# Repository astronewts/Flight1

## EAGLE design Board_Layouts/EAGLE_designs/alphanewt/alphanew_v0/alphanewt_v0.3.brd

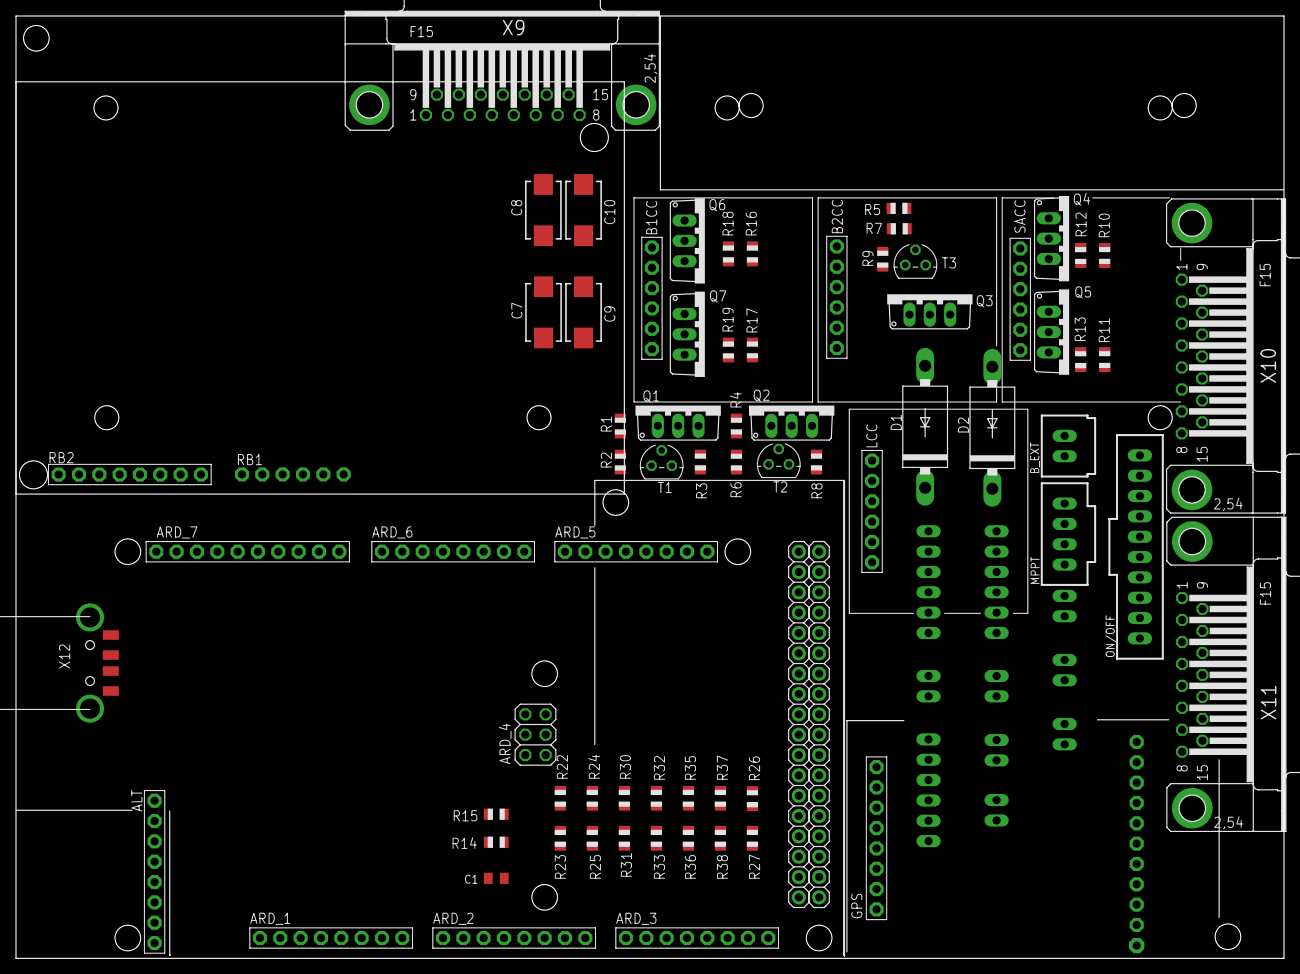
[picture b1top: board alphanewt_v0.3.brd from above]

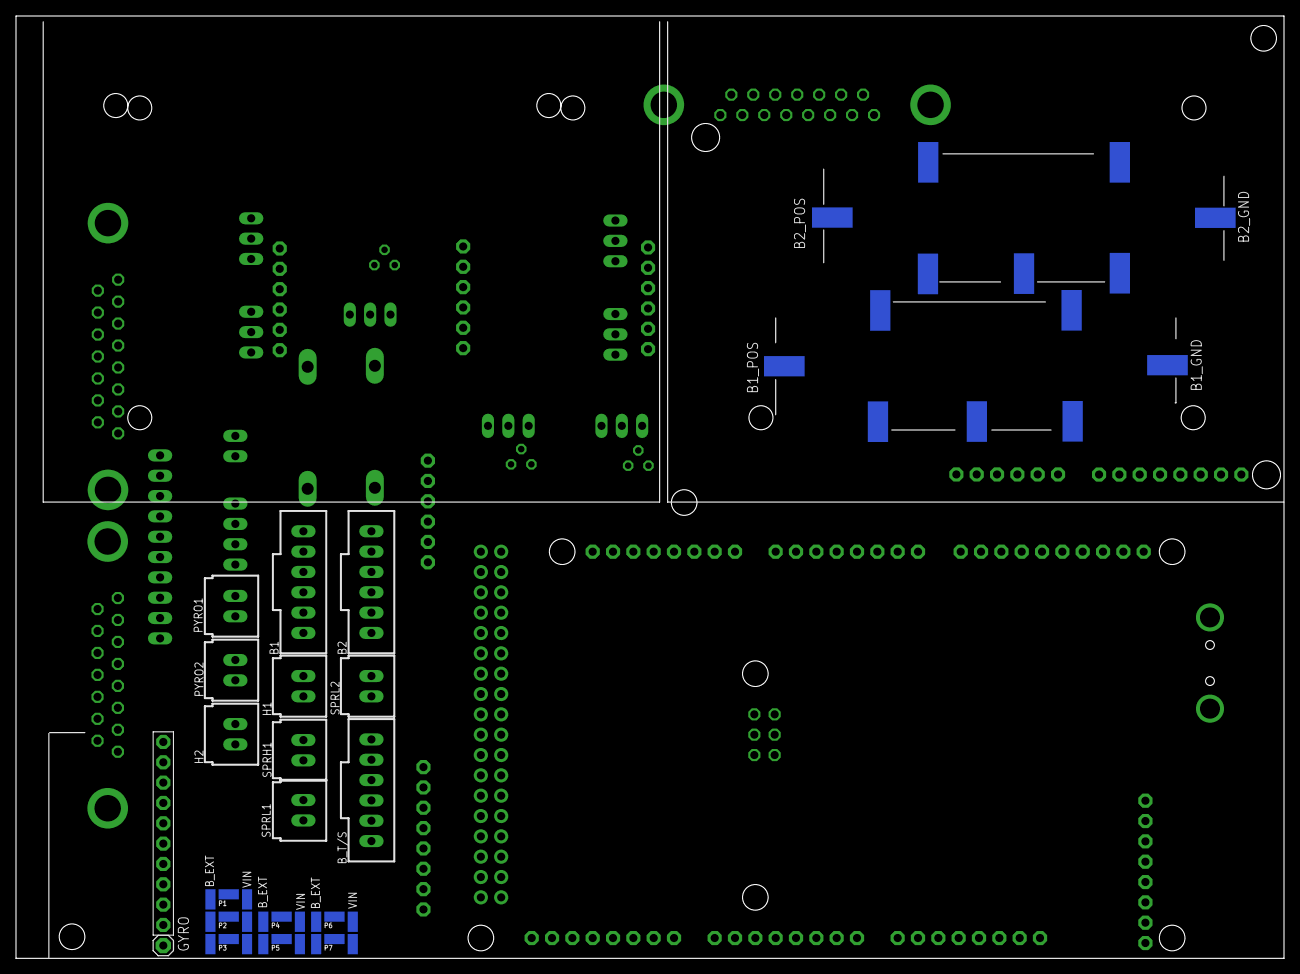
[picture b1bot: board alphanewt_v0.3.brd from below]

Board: 2 copper layers, 158.4 x 117.7 mm, 121 parts (47 on the bottom side), 80 nets, no tracks yet.

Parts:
ALT: 1X08-BIG
ARD_1, ARD_2, ARD_3, ARD_5, ARD_6: 1X08-BIG
ARD_4: 2X03
ARD_7: PINHD-1X10; 1X10-BIG
ARD_8, ARD_9: 1X18-BIG
B1, B2: C-GRID-06-70543; 70543-06
B1CC, B2CC: 1X06-BIG
B1_CELL_1, B1_CELL_2, B1_CELL_3, B1_GND, B1_IN_NEG, B1_IN_POS, B1_POS, B2_CELL_1, B2_CELL_2, B2_GND, B2_IN_NEG, B2_IN_POS, B2_POS, B3_CELL_3: SMD2,54-5,08
B_EXT: C-GRID-02-70543; 70543-02
B_T/S: C-GRID-06-70543; 70543-06
C1: 4.7uF; C0805K
C7, C8, C9, C10: CT7343
D1, D2: 1N5400; DO201-15
GPS: 1X08-BIG
GYRO: PINHD-1X10; 1X10-BIG
GYRO_2: 1X01
H1, H2: C-GRID-02-70543; 70543-02
LCC: 1X06-BIG
MPPT: C-GRID-04-70543; 70543-04
ON/OFF: C-GRID-10-70543; 70543-10
PEXT1, PEXT2, PEXT3, PEXT4, PEXT5, PEXT6, PEXT7: SMD1,27-2,54
PO1, PO2, PO3, PO4, PO5, PO6, PO7: SMD1,27-2,54
PVIN1, PVIN2, PVIN3, PVIN4, PVIN5, PVIN6, PVIN7: SMD1,27-2,54
PYRO1, PYRO2: C-GRID-02-70543; 70543-02
Q1, Q2, Q3, Q4, Q5, Q6, Q7: TIP41C; TO220AV
R1, R2, R3, R4, R5, R6, R7, R8, R9: 150; R0805
R10, R11, R16, R17: 120; R0805
R12, R13, R18, R19: 10k; R0805
R14: 1.7M; R0805
R15: 470k; R0805
R22, R24, R26, R30, R32, R35, R37: 6800; R0805
R23, R25, R27, R31, R33, R36, R38: 120000; R0805
RB1: 1X06-CLEANBIG
RB2: 1X08-BIG
SACC: 1X06-BIG
SPRH1: C-GRID-02-70543; 70543-02
SPRL1, SPRL2: C-GRID-02-70543; 70543-02
T1, T2, T3: 2N3904; TO92
X9, X10, X11: F15HP
X12: USB-A; MOLEX_480371000

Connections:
+3.3V: ALT.2, ARD_1.4, B1CC.1, B2CC.1, GPS.1, LCC.1, SACC.1
+5V: ARD_1.5, ARD_8.1, ARD_9.1, R22.2, R24.2, R26.2, R30.2, R32.2, R35.2, R37.2, RB2.2
ALT_CS: ALT.7, ARD_8.7
ALT_MISO: ALT.5, ARD_8.9
ALT_MOSI: ALT.6, ARD_8.8
ALT_SCK: ALT.4, ARD_8.10
B1_CHRG_IN: B1.1, B1CC.6, B1_POS.1, C7.+, C9.+
B1_CHRG_OUT: B1CC.5, B2CC.5, ON/OFF.1
B1_GND: B1.6, B1_GND.1, C7.-, C9.-, ON/OFF.2
B1_TO_LOAD: D1.A, ON/OFF.5
B2_CHRG_IN: B2.1, B2CC.6, B2_POS.1, C8.+, C10.+
B2_GND: B2.6, B2_GND.1, C8.-, C10.-, ON/OFF.4
B2_TO_LOAD: D2.A, ON/OFF.7
BATT_1_TS1: ARD_3.1, B_T/S.1, R30.1, R31.2
BATT_1_TS2: ARD_3.2, B_T/S.3, R32.1, R33.2
BATT_2_TS1: ARD_3.3, B_T/S.4, R35.1, R36.2
BATT_2_TS2: ARD_3.4, B_T/S.6, R37.1, R38.2
BATT_CHRG_PWR: B1_IN_POS.1, B2_IN_POS.1, MPPT.1
BATT_CHRG_PWR_RTN: B1_IN_NEG.1, B2_IN_NEG.1, MPPT.2
BATT_EXT_PWR: B_EXT.1, PEXT1.1, PEXT2.1, PEXT3.1, PEXT4.1, PEXT5.1, PEXT6.1, PEXT7.1, X10.1, X10.3
CUTDOWN_1_FIRE: ARD_6.5, R1.2
CUTDOWN_2_FIRE: ARD_6.4, R4.2
FLT_CMP_TEMP: ARD_2.7, R26.1, R27.2
GND: ALT.3, ARD_1.6, ARD_1.7, ARD_7.4, ARD_8.18, ARD_9.18, B1CC.2, B2CC.2, B_EXT.2, B_T/S.2, B_T/S.5, C1.2, GPS.8, GYRO.1, LCC.2, ON/OFF.6, ON/OFF.8, ON/OFF.10, Q1.E, Q2.E, Q3.E, Q4.E, Q5.E, Q6.E, Q7.E, R3.1, R8.1, R9.1, R12.1, R13.1, R15.1, R18.1, R19.1, R23.1, R25.1, R27.1, R31.1, R33.1, R36.1, R38.1, RB1.6, RB2.1, RB2.8, SACC.2, X9.2, X9.4, X10.2, X10.4, X12.4
GYRO_PWR: ARD_8.5, GYRO.2
HEATER_1_PWR: H1.1, PO4.1, X11.8
HEATER_1_PWR_RTN: H1.2, Q4.C, X11.9
HEATER_2_PWR: H2.1, PO5.1, X11.10
HEATER_2_PWR_RTN: H2.2, Q5.C, X11.11
HEATER_CONTROL_1: ARD_7.10, R10.2
HEATER_CONTROL_2: ARD_6.3, R11.2
LOAD_IN: D1.C, D2.C, LCC.6
MISO: ARD_4.1, ARD_7.6
MOSI: ARD_4.4, ARD_7.7
unnamed: R4.1, R6.2, T2.2
unnamed: R1.1, R2.2, T1.2
unnamed: Q4.B, R10.1, R12.2
unnamed: Q2.B, R6.1, R8.2, T2.3
unnamed: Q5.B, R11.1, R13.2
unnamed: Q1.B, R2.1, R3.2, T1.3
unnamed: Q6.B, R16.1, R18.2
unnamed: R5.1, R7.2, T3.2
unnamed: Q3.B, R7.1, R9.2, T3.3
unnamed: B1.5, B1_CELL_1.1
unnamed: Q7.B, R17.1, R19.2
unnamed: B1.4, B1_CELL_2.1
unnamed: B2.3, B3_CELL_3.1
unnamed: B2.4, B2_CELL_2.1
unnamed: B2.5, B2_CELL_1.1
unnamed: B1.3, B1_CELL_3.1
PYRO_1_PWR: PO1.1, PYRO1.1, X11.1
PYRO_1_PWR_RTN: PYRO1.2, Q1.C, T1.1, X11.2
PYRO_2_PWR: PO2.1, PYRO2.1, X11.3
PYRO_2_PWR_RTN: PYRO2.2, Q2.C, T2.1, X11.4
RESET: ARD_1.3, ON/OFF.9
RX0: ARD_6.8, X12.2
RX1: ARD_5.6, GPS.5
RX3: ARD_5.2, RB1.2
S/A_PWR_IN: SACC.6, X10.6, X10.8, X10.10
S/A_PWR_OUT: MPPT.3, SACC.5
S/A_PWR_RTN: MPPT.4, X10.7, X10.9, X10.11
SCK: ARD_4.3, ARD_7.5
SCL: ARD_5.8, B1CC.3, B2CC.3, GYRO.4, LCC.3, SACC.3
SDA: ARD_5.7, B1CC.4, B2CC.4, GYRO.3, LCC.4, SACC.4
SPARE_1_PWR: PO6.1, SPRL1.1, X11.12
SPARE_1_PWR_RTN: Q6.C, SPRL1.2, X11.13
SPARE_2_PWR: PO7.1, SPRL2.1, X11.14
SPARE_2_PWR_RTN: Q7.C, SPRL2.2, X11.15
SPARE_HIGH_1_CONTROL: ARD_9.2, R5.2
SPARE_HIGH_1_PWR: PO3.1, SPRH1.1, X11.5
SPARE_HIGH_1_PWR_RTN: Q3.C, SPRH1.2, T3.1, X11.6
SPARE_LOW_1_CONTROL: ARD_9.3, R16.2
SPARE_LOW_2_CONTROL: ARD_9.4, R17.2
TEMP_EXT_1: ARD_2.8, R22.1, R23.2, X9.1
TEMP_EXT_2: ARD_2.6, R24.1, R25.2, X9.3
TX0: ARD_6.7, X12.3
TX1: ARD_5.5, GPS.4
TX3: ARD_5.1, RB1.3
VIN: ARD_1.8, LCC.5, PVIN1.1, PVIN2.1, PVIN3.1, PVIN4.1, PVIN5.1, PVIN6.1, PVIN7.1, R14.2
VIN_VOLTAGE_TLM: ARD_2.4, C1.1, R14.1, R15.2
